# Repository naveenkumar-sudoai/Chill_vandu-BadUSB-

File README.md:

# RP2040 Custom USB Interface Board (Chill Vandu)

A custom, ultra-compact RP2040-based USB interface board designed in KiCad. This board is tailored for JLCPCB SMT assembly and features USB-C, a microSD card slot (4-bit SDIO), 3 mode buttons, 3 status LEDs, and 16 MB QSPI flash.

## 📋 Project Status
- [x] Component selection & LCSC verification
- [x] Custom symbol, footprint, and 3D model generation (using `easyeda2kicad`)
- [x] Schematic capture (ERC Clean: 0 Errors)
- [ ] PCB Layout & Routing (In Progress)
- [ ] Gerber & BOM/CPL Generation
- [ ] JLCPCB Assembly & Bring-up

## 🛠️ Technical Specifications
Based on the Raspberry Pi Hardware Design guide with specific engineering modifications:
*   **MCU:** RP2040 (`C2040`) QFN-56.
*   **Power:** 500mA LDO LW5433A23E (`C20630445`) in SOT-23-5L. *Upgraded from the 200mA XC6206 to handle SD card write bursts.*
*   **USB:** USB-C 16-pin HRO TYPE-C-31-M-12 (`C165948`) with 5.1kΩ CC pulldowns, 27Ω series resistors on D+/D-, and USBLC6-2SC6 (`C7519`) ESD protection.
*   **Storage:** W25Q128JVSIQ 16MB QSPI Flash (`C97521`) and SHOU HAN TF PUSH microSD (`C393941`).
*   **User I/O:** 3 Mode buttons, 1 BOOTSEL button, 1 RESET button, and 3 Status LEDs (Red, Green, Blue).
*   **LED Circuit:** Simplified direct GPIO drive (No MOSFETs) to reduce BOM cost and board size.
*   **Expansion:** 4-pin I2C breakout (SDA, SCL, 3V3, GND) for future OLED screen/display integration. Currently unpopulated (through-holes only) to save space on the first iteration.
*   **Debugging:** 3x SWD Test Points (SWCLK, SWD, GND) for hardware recovery.

## 💻 Tools Used
*   **KiCad 10**
*   **easyeda2kicad** (for exact LCSC footprint matching)
*   **JLCPCB** (for fabrication and assembly)

## 🔗 References
*   Raspberry Pi Hardware Design with RP2040
*   JLCPCB Fabrication Toolkit

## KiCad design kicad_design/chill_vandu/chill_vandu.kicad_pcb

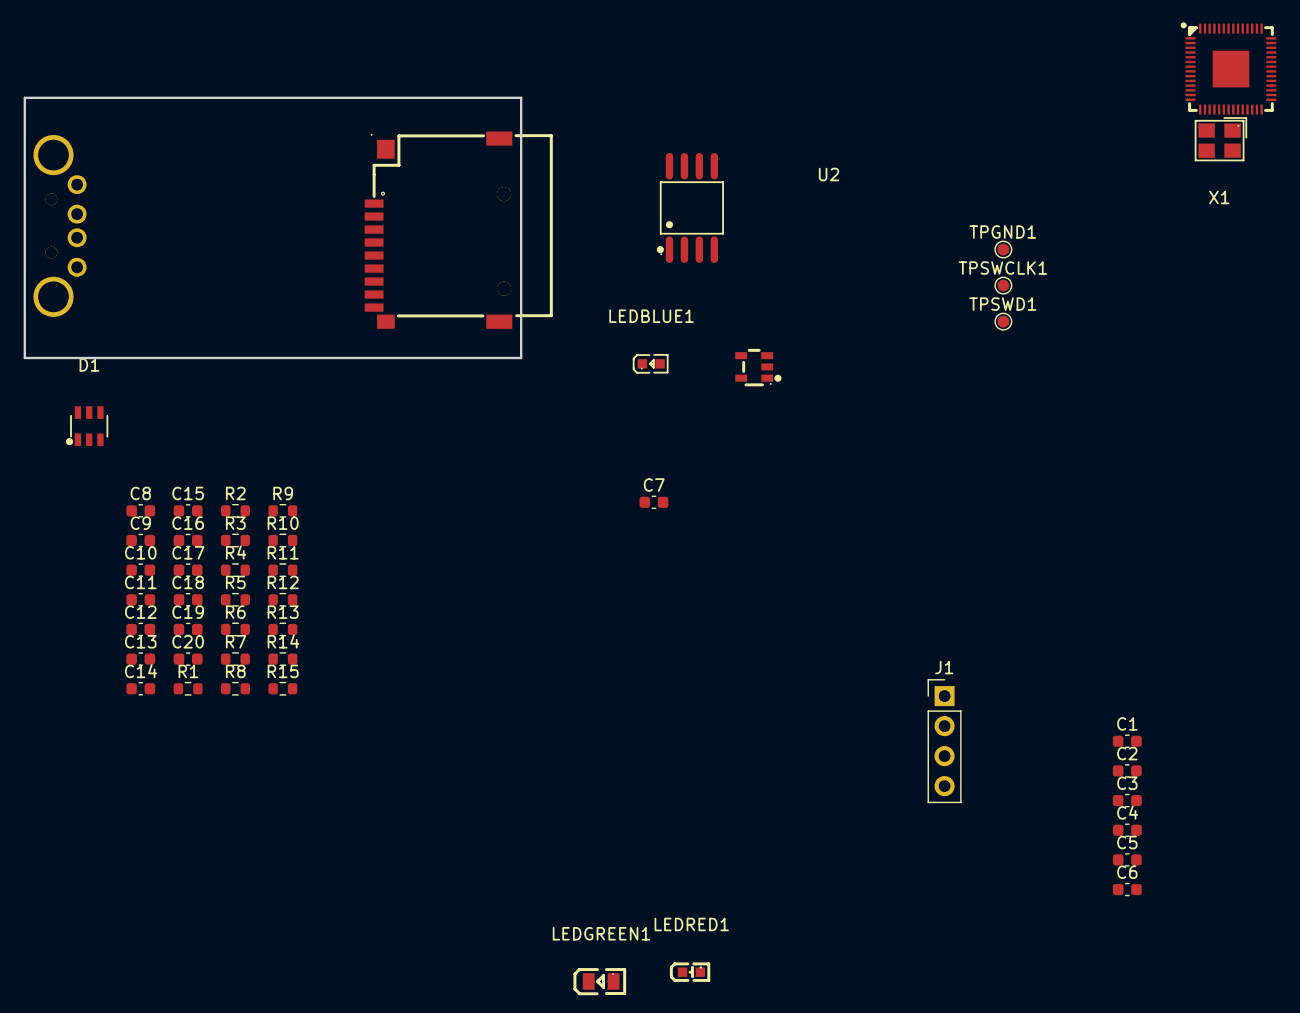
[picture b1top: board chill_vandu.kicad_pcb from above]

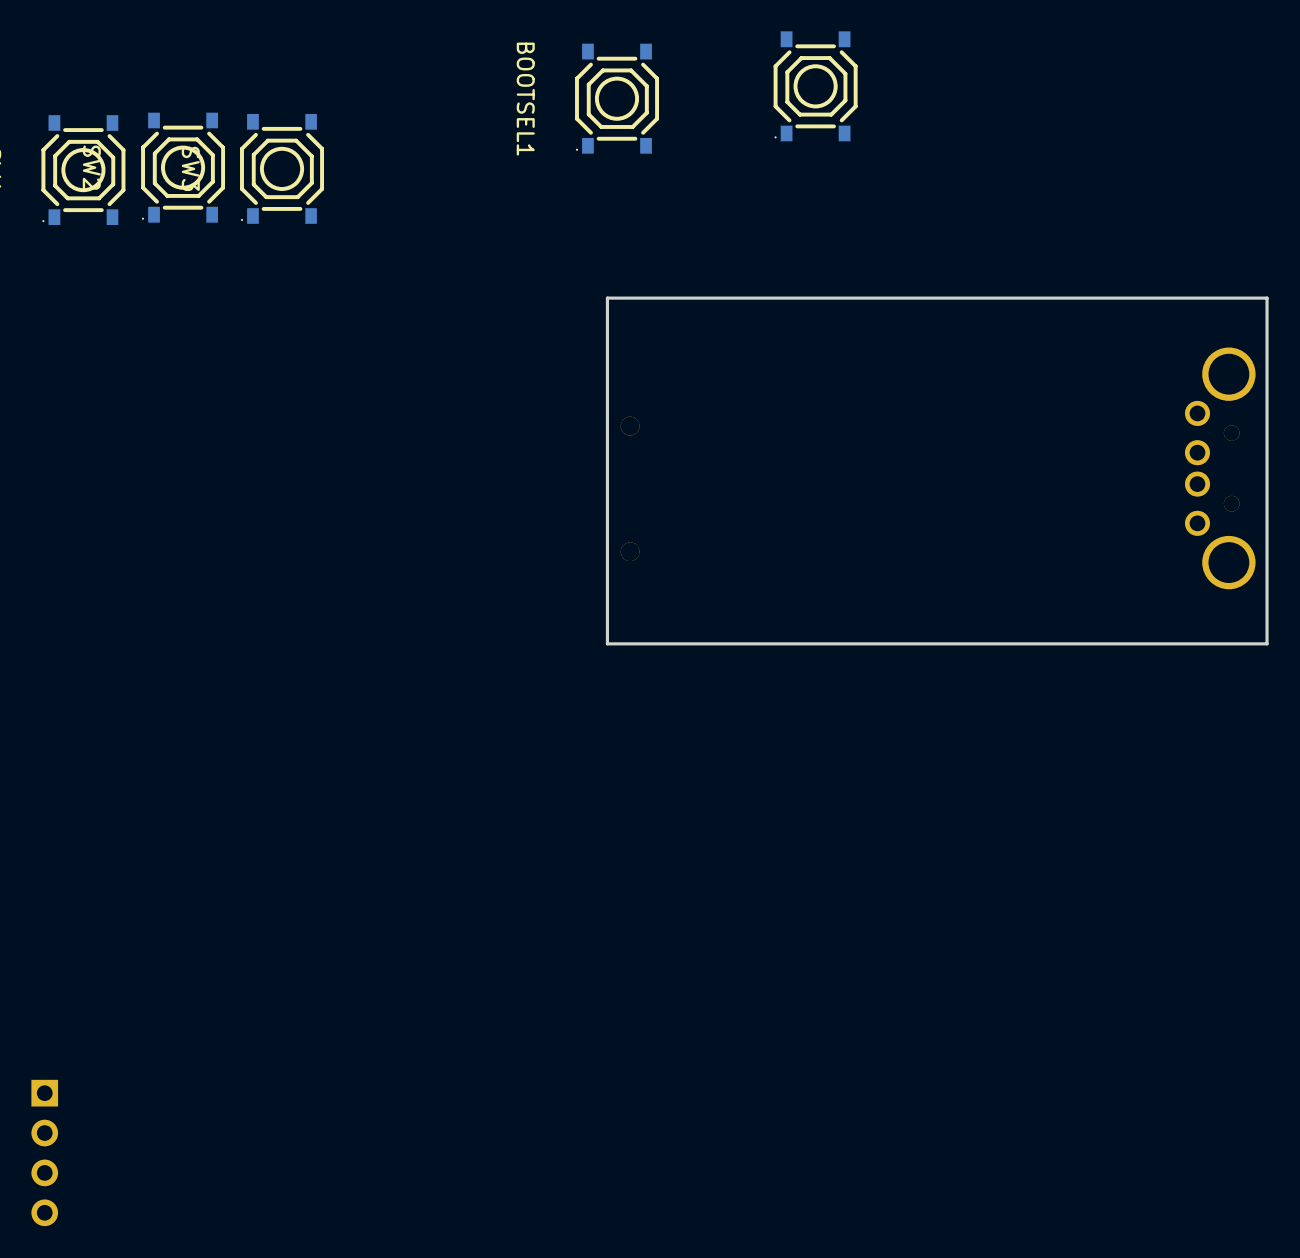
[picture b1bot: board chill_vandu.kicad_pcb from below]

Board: 2 copper layers, 42.0 x 22.0 mm, 54 parts (5 on the bottom side), 39 nets, no tracks yet.

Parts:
BOOTSEL1: TS-1187A-B-A-B; SW-SMD_4P-L5.1-W5.1-P3.70-LS6.5-TL_H1.5
C1, C3, C6, C8, C9, C10, C11, C12, C13, C15, C18, C19: 100nF; C_0603_1608Metric
C2, C14: 10uF; C_0603_1608Metric
C4, C5, C7, C20: 1uF; C_0603_1608Metric
C16, C17: 27pF; C_0603_1608Metric
Card1: TF PUSH; TF-SMD_TF-PUSH
D1: USBLC6-2SC6; SOT-23-6_L2.9-W1.6-P0.95-LS2.8-BL
J1: Conn_01x04; PinHeader_1x04_P2.54mm_Vertical
LEDBLUE1: Blue light 0603; LED0603-RD
LEDGREEN1: 0805G; LED0805-R-RD
LEDRED1: KT-0603R; LED-SMD_L1.6-W0.8-R-RD
R1, R15: 1kΩ; R_0603_1608Metric
R2, R6, R7, R8, R9, R10: 10kΩ; R_0603_1608Metric
R3: 330Ω; R_0603_1608Metric
R4, R5: 100Ω; R_0603_1608Metric
R11, R12: 27Ω; R_0603_1608Metric
R13, R14: 5.1kΩ; R_0603_1608Metric
SW1, SW2, SW3, SW4: TS-1187A-B-A-B; SW-SMD_4P-L5.1-W5.1-P3.70-LS6.5-TL_H1.5
TPGND1: TestPoint; TestPoint_Pad_D1.0mm
TPSWCLK1: TestPoint; TestPoint_Pad_D1.0mm
TPSWD1: TestPoint; TestPoint_Pad_D1.0mm
U1: W25Q128JVSIQTR; SOIC-8_L5.3-W5.3-P1.27-LS8.0-BL
U2: LW5433A23E; SOT-23-5_L2.9-W1.6-P0.95-LS2.8-BR
U3: RP2040; LQFN-56_L7.0-W7.0-P0.4-EP
USB2: AM90; USB-AM-TH_AM90
X1: X322512MSB4SI; CRYSTAL-SMD_4P-L3.2-W2.5-BL

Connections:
/3V3: C1.2, C2.1, C3.1, C5.1, C6.1, C7.1, C8.1, C9.1, C10.1, C11.1, C12.1, C13.1, C15.1, Card1.4 (VDD), J1.2, LEDBLUE1.2 (A), LEDGREEN1.1 (A), LEDRED1.1 (A), R2.1, R6.1, R7.1, R8.1, R9.1, R10.1, U1.8 (VCC), U2.5 (VOUT), U3.1 (IOVDD), U3.10 (IOVDD), U3.22 (IOVDD), U3.33 (IOVDD), U3.42 (IOVDD), U3.43 (ADC_AVDD), U3.48 (USB_VDD), U3.49 (IOVDD)
/GPIO2: SW3.3 (C), U3.4 (GPIO2)
/GPIO3: SW4.3 (C), U3.5 (GPIO3)
/GPIO4: SW2.3 (C), U3.6 (GPIO4)
/GPIO5: R3.1, U3.7 (GPIO5)
/GPIO6: R5.1, U3.8 (GPIO6)
/GPIO7: R4.1, U3.9 (GPIO7)
/QSPI_SCLK: U1.6 (CLK), U3.52 (QSPI_SCLK)
/QSPI_SD0: U1.5 (DI), U3.53 (QSPI_SD0)
/QSPI_SD1: U1.2 (DO), U3.55 (QSPI_SD1)
/QSPI_SD2: U1.3 (IO2), U3.54 (QSPI_SD2)
/QSPI_SD3: U1.7 (IO3), U3.51 (QSPI_SD3)
/QSPI_SS: BOOTSEL1.1 (A), R2.2, U1.1 (~CS), U3.56 (QSPI_SS)
/RP_USB_DN: R12.2, U3.46 (USB_DM)
/RP_USB_DP: R11.2, U3.47 (USB_DP)
/RUN: SW1.3 (C), U3.26 (RUN)
/SCL: J1.4, U3.28 (GPIO17)
/SDA: J1.3, U3.27 (GPIO16)
/SD_CD: Card1.CD, U3.12 (GPIO9)
/SD_CLK: Card1.5 (CLX), U3.13 (GPIO10)
/SD_CMD: Card1.3 (CMD), R6.2, U3.14 (GPIO11)
/SD_D0: Card1.7 (DAT0), R7.2, U3.15 (GPIO12)
/SD_D1: Card1.8 (DAT1), R8.2, U3.16 (GPIO13)
/SD_D2: Card1.1 (DAT2), R9.2, U3.17 (GPIO14)
/SD_D3: Card1.2 (CD/DAT3), R10.2, U3.18 (GPIO15)
/VBUS: C4.1, C14.1, D1.5, U2.1 (VIN), U2.3 (EN)
GND: C1.1, C2.2, C3.2, C4.2, C5.2, C6.2, C7.2, C8.2, C9.2, C10.2, C11.2, C12.2, C13.2, C14.2, C15.2, C16.2, C17.1, C18.1, C19.1, C20.1, Card1.6 (VSS), Card1.10, Card1.11, Card1.12, Card1.13, D1.2, J1.1, R1.1, R13.2, R14.1, SW1.2 (B), SW2.2 (B), SW3.1 (A), SW4.1 (A), TPGND1.1 (1_1), U1.4 (GND), U2.2 (GND), U3.19 (TESTEN), U3.57 (GND), X1.2 (GND), X1.4 (GND)
unnamed: BOOTSEL1.3 (C), R1.2
unnamed: D1.4, R12.1
unnamed: D1.6, R11.1
unnamed: LEDBLUE1.1 (K), R4.2
unnamed: LEDGREEN1.2 (K), R5.2
unnamed: LEDRED1.2 (K), R3.2
unnamed: TPSWCLK1.1 (1_1), U3.24 (SWCLK)
unnamed: TPSWD1.1 (1_1), U3.25 (SWD)
unnamed: C18.2, C19.2, C20.2, U3.23 (DVDD), U3.45 (VREG_VOUT), U3.50 (DVDD)
unnamed: C17.2, U3.20 (XIN), X1.1 (OSC1)
unnamed: R15.2, U3.21 (XOUT)
unnamed: C16.1, R15.1, X1.3 (OSC2)
